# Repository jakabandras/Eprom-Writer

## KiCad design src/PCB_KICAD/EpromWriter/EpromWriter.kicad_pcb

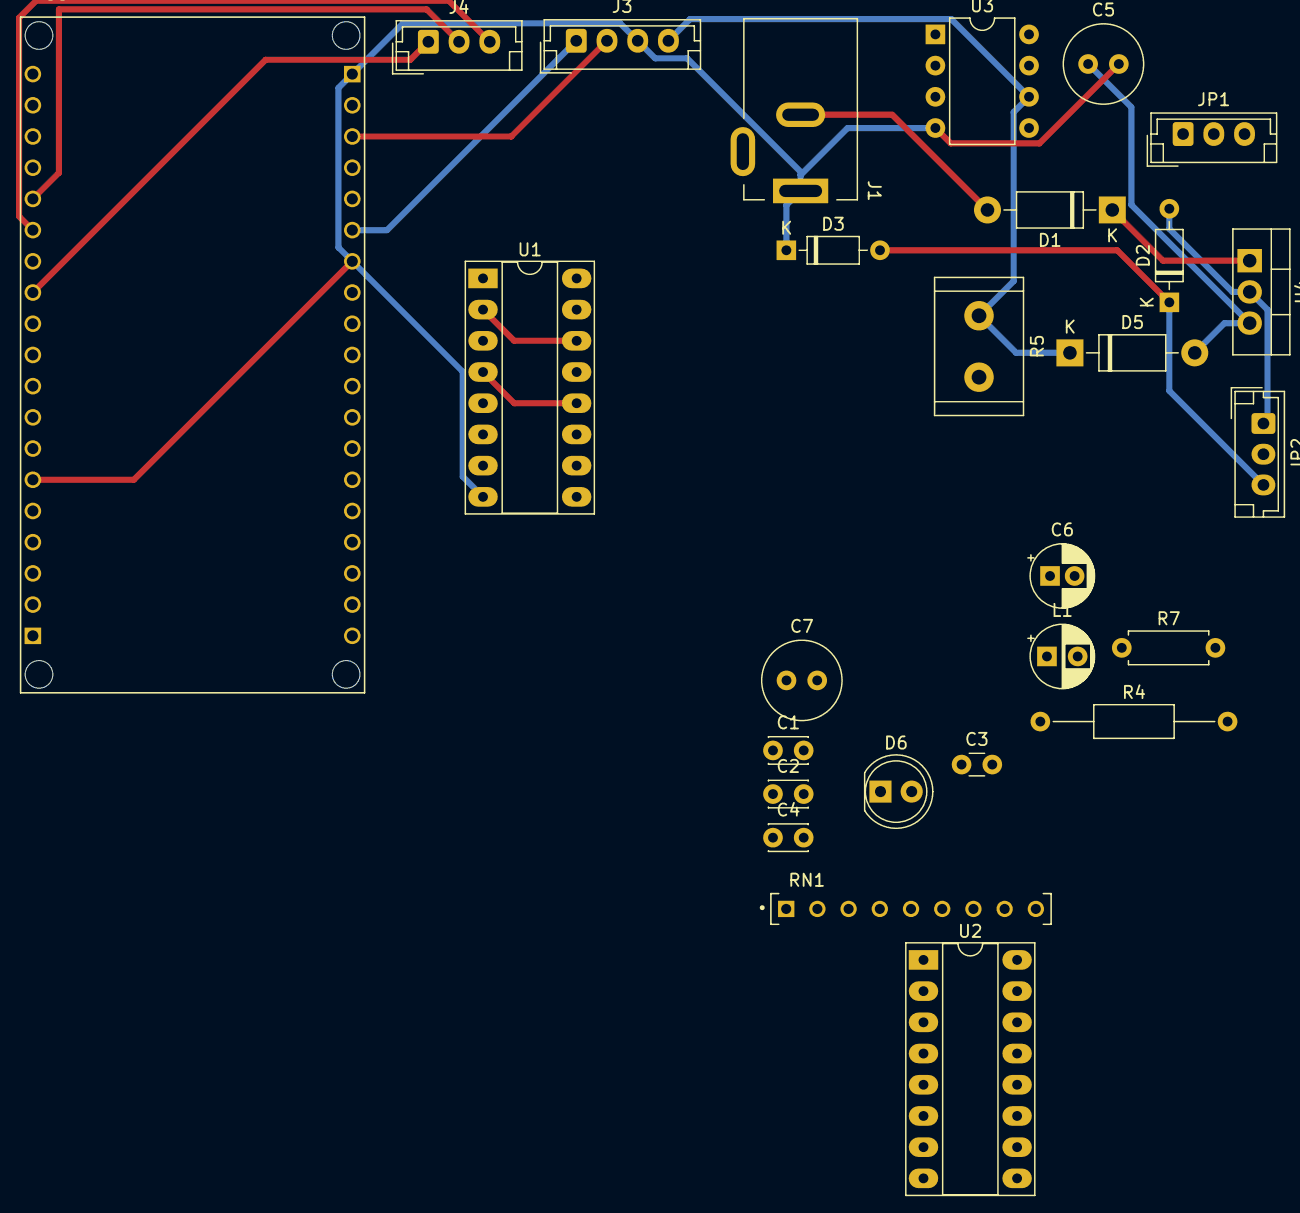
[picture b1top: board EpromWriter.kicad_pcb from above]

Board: 2 copper layers, 27 parts (0 on the bottom side), 23 nets.

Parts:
C1, C2, C4: 100n; C_Disc_D3.0mm_W2.0mm_P2.50mm
C3: 1n; C_Disc_D3.0mm_W1.6mm_P2.50mm
C5: 3.3u; C_Radial_D6.3mm_H5.0mm_P2.50mm
C6: 47u/35v; CP_Radial_D5.0mm_P2.00mm
C7: 33u; C_Radial_D6.3mm_H5.0mm_P2.50mm
D1, D5: 1N4001; D_DO-41_SOD81_P10.16mm_Horizontal
D2, D3: 1N4148; D_DO-35_SOD27_P7.62mm_Horizontal
D6: RED; LED_D5.0mm
J1: Barrel_Jack; BarrelJack_Kycon_KLDX-0202-xC_Horizontal
J3: Conn_01x04_Pin; JST_EH_B4B-EH-A_1x04_P2.50mm_Vertical
J4: Conn_01x03_Pin; JST_EH_B3B-EH-A_1x03_P2.50mm_Vertical
JP1, JP2: Jumper_3_Bridged12; JST_EH_B3B-EH-A_1x03_P2.50mm_Vertical
L1: 100uH; CP_Radial_D5.0mm_P2.50mm
R4: 220; R_Axial_DIN0207_L6.3mm_D2.5mm_P15.24mm_Horizontal
R5: 0.33/10W; R_Radial_Power_L11.0mm_W7.0mm_P5.00mm
R7: 1.2k; R_Axial_DIN0207_L6.3mm_D2.5mm_P7.62mm_Horizontal
RN1: 4609X-101-103LF; SIP249W50P254L2281H508Q9
U1, U2: 74LS367; DIP-16_W7.62mm_Socket_LongPads
U3: MC34063AP; DIP-8_W7.62mm
U4: LM7805_TO220; TO-220-3_Vertical
U5: ESP32_NODEMCU; MODULE_ESP32_NODEMCU

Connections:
+5V: U1.16 (VCC), U2.16 (VCC)
+12V: D1.2 (A), J1.2
/DO0: RN1.2, U1.2 (I1), U1.14 (I6)
/DO1: RN1.3, U1.4 (I2), U1.12 (I5)
/DO2: RN1.4, U1.6 (I3)
/DO3: RN1.5, U1.10 (I4)
/MCU/SCL: J3.2, U5.J4_3 (G22)
/MCU/SDA: J3.1, U5.J4_6 (G21)
/MCU/encA: J4.1, U5.J5_12 (G33)
/MCU/encB: J4.2, U5.J5_15 (G34)
/MCU/encButton: J4.3, U5.J5_14 (G35)
GNDREF: C1.2, C2.2, C3.1, C4.2, C5.2, C6.2, C7.2, D3.1 (K), D6.1 (K), J1.1, J3.3, JP2.2 (C), U1.8 (GND), U2.8 (GND), U3.2 (SwE), U3.4 (GND), U5.J4_1 (GND_J4_1), U5.J4_7 (GND_J4_7), U5.J5_6 (GND_J5_6)
unnamed: D1.1 (K), U4.1 (VI)
unnamed: D2.2 (A), JP2.1 (A), U4.2 (GND)
unnamed: D2.1 (K), D3.2 (A), JP2.3 (B)
unnamed: L1.1, U3.1 (SwC)
unnamed: C4.1, C5.1, D5.2 (A), U4.3 (VO)
unnamed: D6.2 (A), R7.2
unnamed: JP1.2 (C), JP1.3 (B)
unnamed: R4.1, U3.8 (DC)
unnamed: L1.2, R4.2, R5.2, U3.7 (Ipk)
unnamed: C3.2, U3.3 (TC)
VCC: C1.1, C2.1, C7.1, D5.1 (K), J3.4, R5.1, R7.1, RN1.1, U3.6 (Vin), U5.J5_1 (5V)

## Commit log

2023-08-07 Kezdet
2023-08-07 Kezdeti KiCAD fájlok létrehozása
2023-08-10 Haladás a projekttel
2023-08-11 Added json eprom database and begin the pcb design
2023-08-16 Menü hozzáadása és néhány apróbb változtatás
2023-08-17 Kiinduló állapot:
